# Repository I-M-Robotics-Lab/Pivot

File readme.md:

Discord: https://discord.com/invite/WJuUWsy6DJ

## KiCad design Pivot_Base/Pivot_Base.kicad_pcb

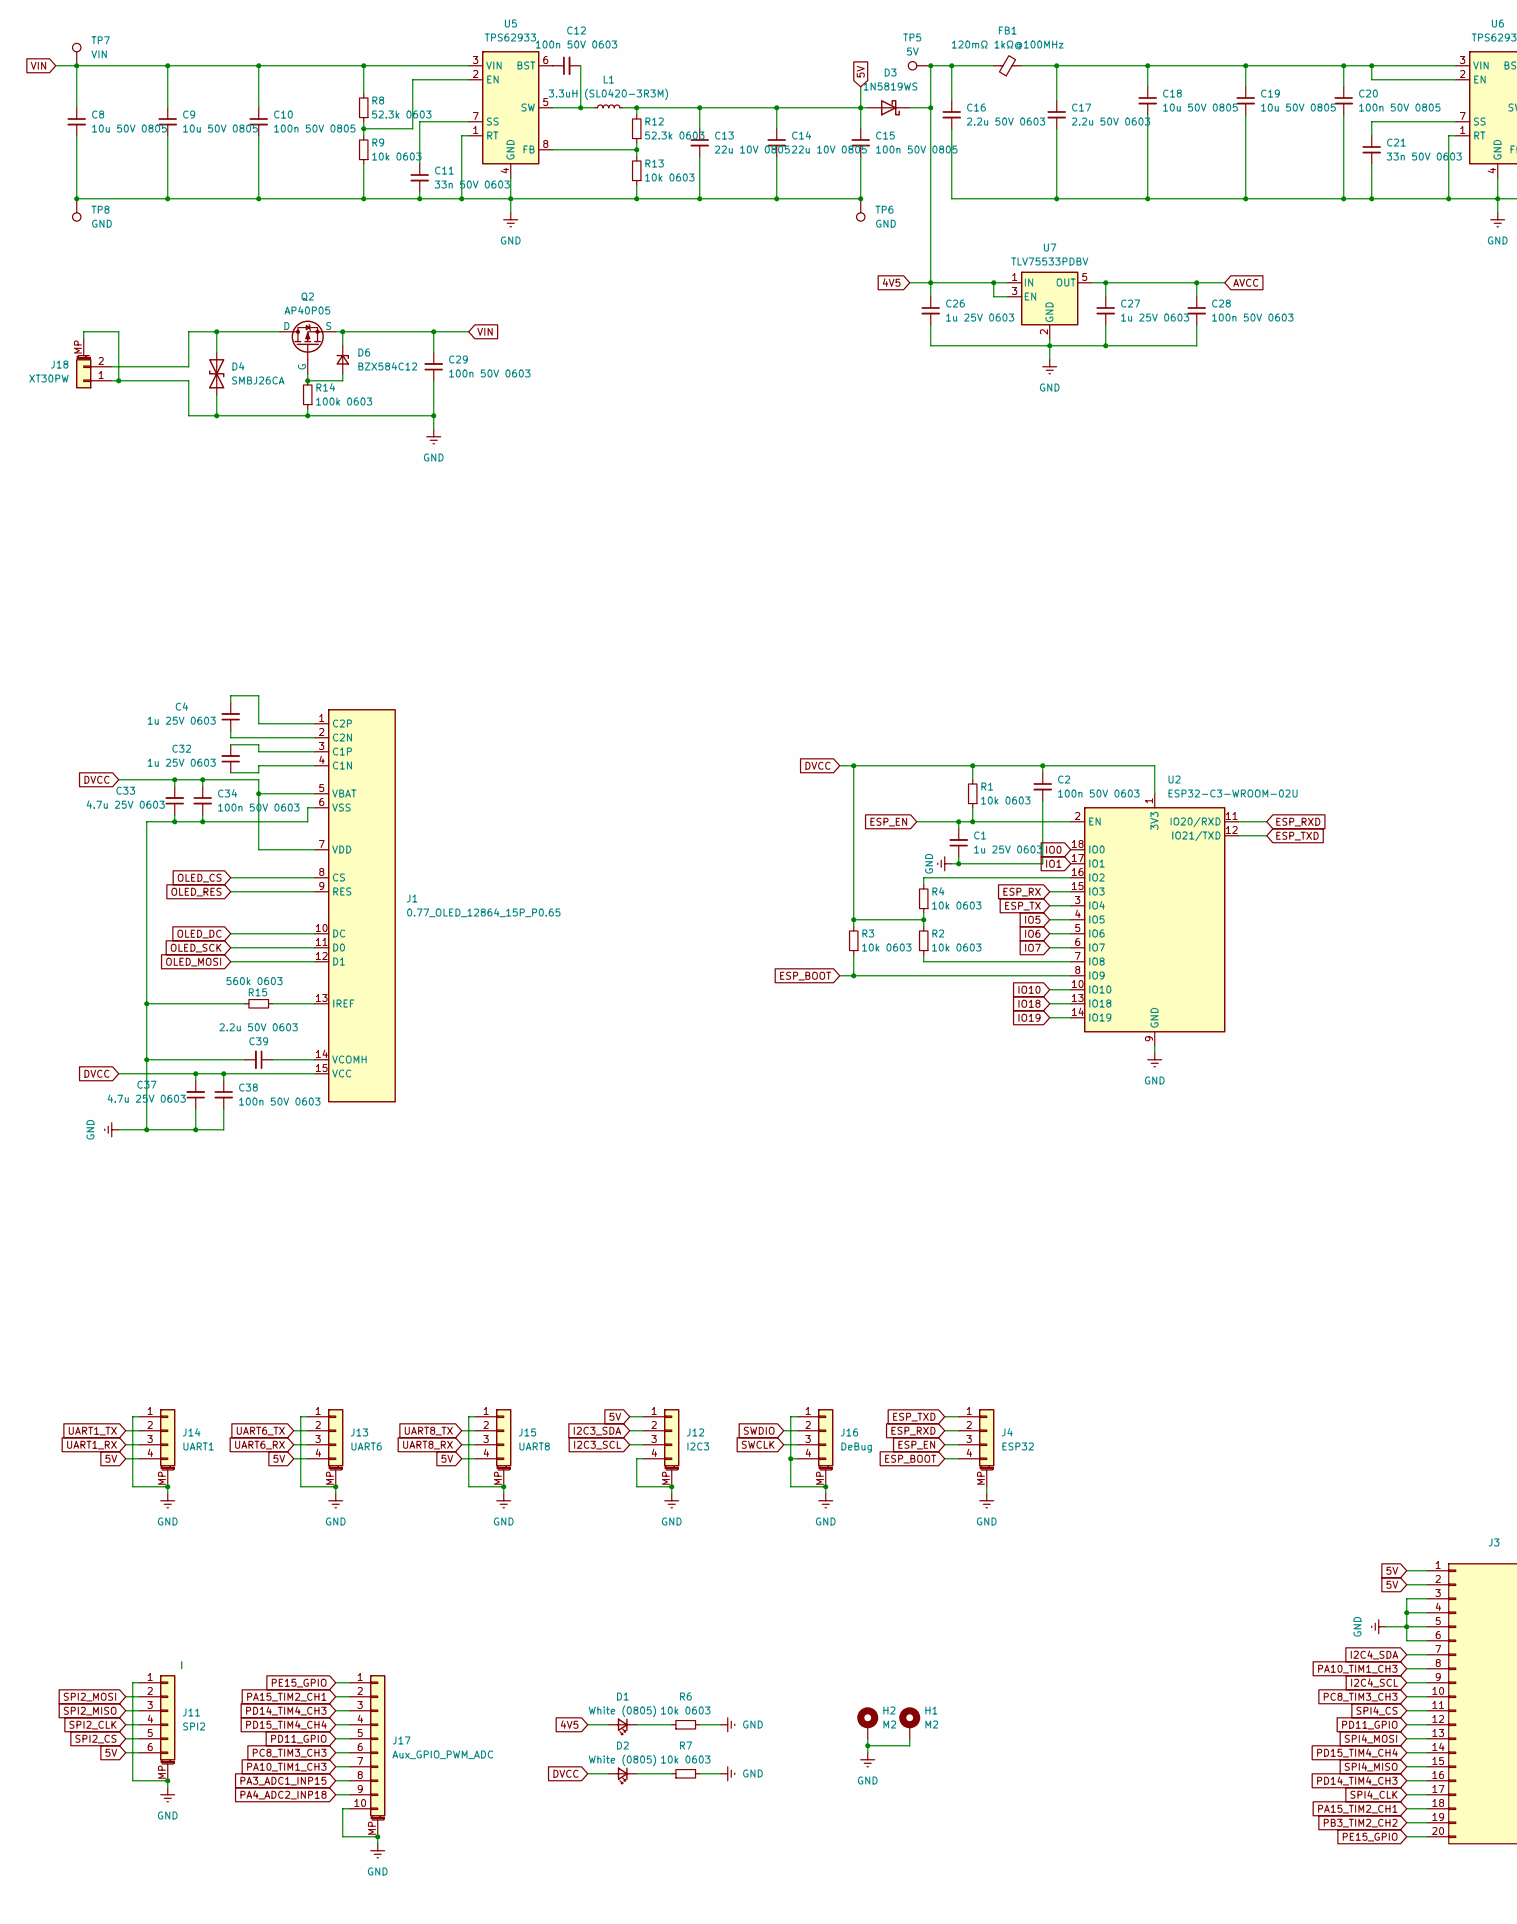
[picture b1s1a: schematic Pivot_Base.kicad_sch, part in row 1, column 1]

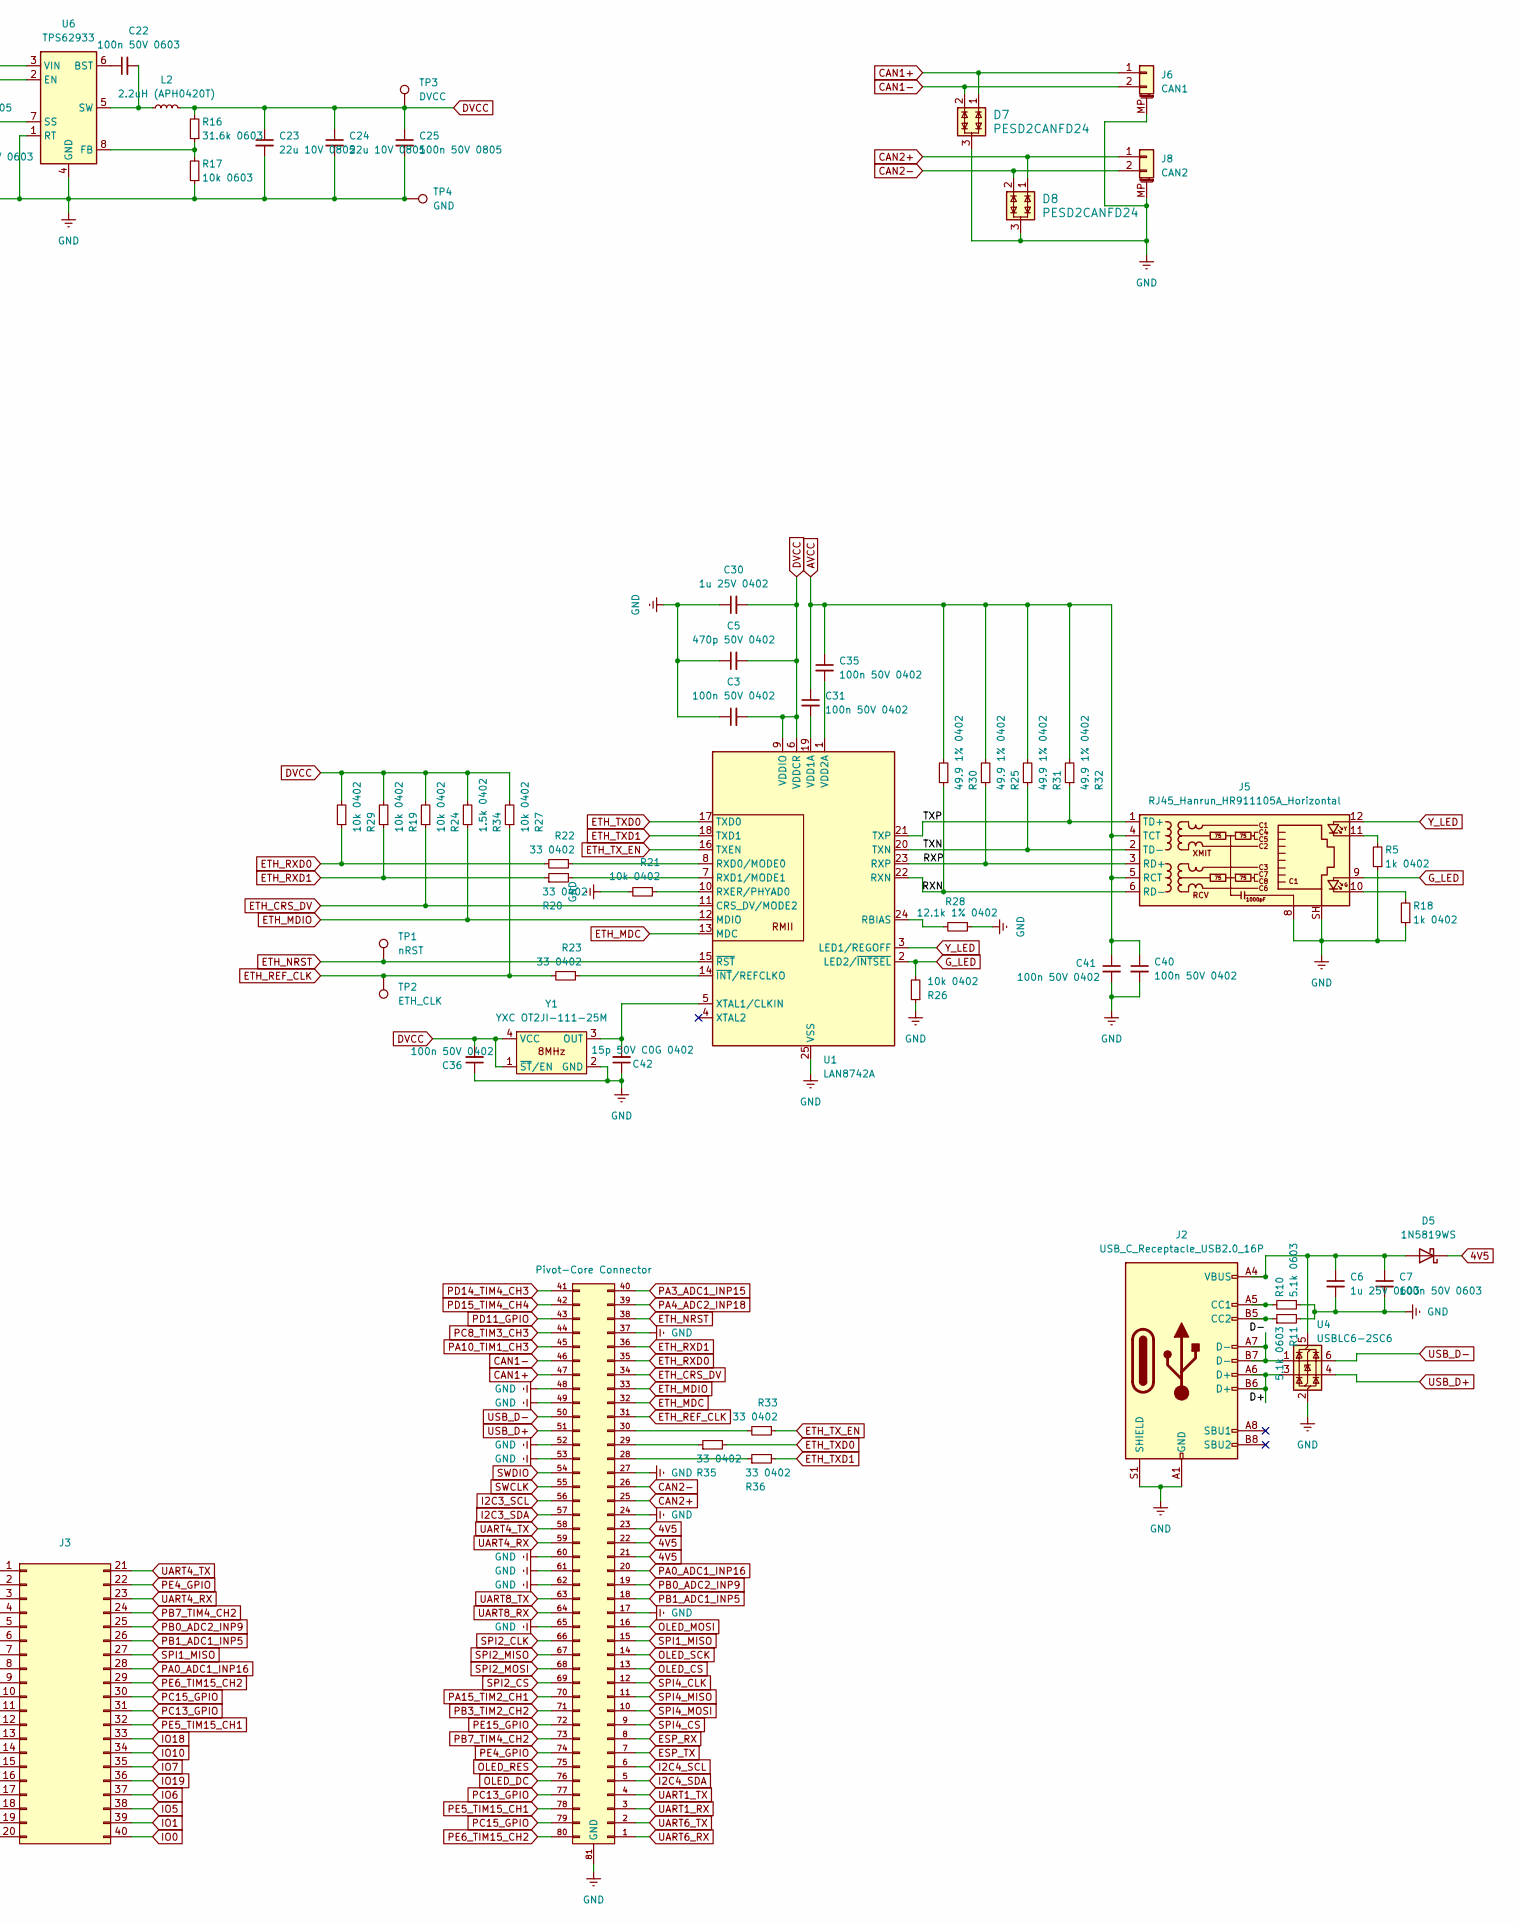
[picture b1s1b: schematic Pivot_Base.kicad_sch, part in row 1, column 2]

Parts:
C1, C4, C6, C26, C27, C32: 1u 25V 0603; C_0603_1608Metric
C2, C7, C12, C22, C28, C29, C34, C38: 100n 50V 0603; C_0603_1608Metric
C3, C31, C35, C36, C40, C41: 100n 50V 0402; C_0402_1005Metric
C5: 470p 50V 0402; C_0402_1005Metric
C8, C9, C18, C19: 10u 50V 0805; C_0805_2012Metric
C10, C15, C20, C25: 100n 50V 0805; C_0805_2012Metric
C11, C21: 33n 50V 0603; C_0603_1608Metric
C13, C14, C23, C24: 22u 10V 0805; C_0805_2012Metric
C16, C17, C39: 2.2u 50V 0603; C_0603_1608Metric
C30: 1u 25V 0402; C_0402_1005Metric
C33, C37: 4.7u 25V 0603; C_0603_1608Metric
C42: 15p 50V C0G 0402; C_0402_1005Metric
D1, D2: White (0805); LED_0805_2012Metric
D3, D5: 1N5819WS; D_SOD-323
D4: SMBJ26CA; D_SMB
D6: BZX584C12; D_SOD-523
D7, D8: PESD2CANFD24; SOT-23
FB1: 120mΩ 1kΩ@100MHz; R_0805_2012Metric
H1, H2: M2; MountingHole_2.2mm_M2_DIN965_Pad
J1: 0.77_OLED_12864_15P_P0.65
J2: USB_C_Receptacle_USB2.0_16P; USB_C_Receptacle_G-Switch_GT-USB-7010ASV
J3: PinHeader_2x20_P2.54mm_Vertical
J4: ESP32; JST_SH_SM04B-SRSS-TB_1x04-1MP_P1.00mm_Horizontal
J5: RJ45_Hanrun_HR911105A_Horizontal; HANRUN_HR911105A
J6: CAN1; JST_SH_SM02B-SRSS-TB_1x02-1MP_P1.00mm_Horizontal
J7: Pivot-Core Connector; Pivot-Core
J8: CAN2; JST_SH_SM02B-SRSS-TB_1x02-1MP_P1.00mm_Horizontal
J11: SPI2; JST_SH_SM06B-SRSS-TB_1x06-1MP_P1.00mm_Horizontal
J12: I2C3; JST_SH_SM04B-SRSS-TB_1x04-1MP_P1.00mm_Horizontal
J13: UART6; JST_SH_SM04B-SRSS-TB_1x04-1MP_P1.00mm_Horizontal
J14: UART1; JST_SH_SM04B-SRSS-TB_1x04-1MP_P1.00mm_Horizontal
J15: UART8; JST_SH_SM04B-SRSS-TB_1x04-1MP_P1.00mm_Horizontal
J16: DeBug; JST_SH_SM04B-SRSS-TB_1x04-1MP_P1.00mm_Horizontal
J17: Aux_GPIO_PWM_ADC; JST_SH_SM10B-SRSS-TB_1x10-1MP_P1.00mm_Horizontal
J18: XT30PW; AMASS_XT30PW-M_1x02_P2.50mm_Horizontal
L1: 3.3uH (SL0420-3R3M); L_Chilisin_BMRA00040420
L2: 2.2uH (APH0420T); L_APV_APH0420
Q2: AP40P05; SOT-23
R1, R2, R3, R4, R6, R7, R9, R13, R17: 10k 0603; R_0603_1608Metric
R5, R18: 1k 0402; R_0402_1005Metric
R8, R12: 52.3k 0603; R_0603_1608Metric
R10, R11: 5.1k 0603; R_0603_1608Metric
R14: 100k 0603; R_0603_1608Metric
R15: 560k 0603; R_0603_1608Metric
R16: 31.6k 0603; R_0603_1608Metric
R19, R21, R24, R26, R27, R29: 10k 0402; R_0402_1005Metric
R20, R22, R23, R33, R35, R36: 33 0402; R_0402_1005Metric
R25, R30, R31, R32: 49.9 1% 0402; R_0402_1005Metric
R28: 12.1k 1% 0402; R_0402_1005Metric
R34: 1.5k 0402; R_0402_1005Metric
TP1: nRST; TestPoint_Pad_D0.4mm
TP2: ETH_CLK; TestPoint_Pad_D0.4mm
TP3: DVCC; TestPoint_Pad_D0.4mm
TP4, TP6, TP8: GND; TestPoint_Pad_D0.4mm
TP5: 5V; TestPoint_Pad_D0.4mm
TP7: VIN; TestPoint_Pad_D0.4mm
U1: LAN8742A; VQFN-24-1EP_4x4mm_P0.5mm_EP2.5x2.5mm_ThermalVias
U2: ESP32-C3-WROOM-02U
U4: USBLC6-2SC6; SOT-23-6
U5, U6: TPS62933; SOT-583-8
U7: TLV75533PDBV; SOT-23-5
Y1: YXC OT2JI-111-25M; Crystal_SMD_3225-4Pin_3.2x2.5mm

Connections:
4V5: C16.1, C26.1, D1.2 (A), D3.1 (K), D5.1 (K), FB1.1, J7.21, J7.22, J7.23, TP5.1, U7.1 (IN), U7.3 (EN)
5V: C13.1, C14.1, C15.1, D3.2 (A), J3.1, J3.2, J11.6, J12.1, J13.4, J14.4, J15.4, L1.2, R12.2
/D+: J2.A6 (D+), J2.B6 (D+), U4.3 (I/O2)
/D-: J2.A7 (D-), J2.B7 (D-), U4.1 (I/O1)
/RXN: J5.6 (RD-), R30.1, U1.22 (RXN)
/RXP: J5.3 (RD+), R25.1, U1.23 (RXP)
/TXN: J5.2 (TD-), R31.1, U1.20 (TXN)
/TXP: J5.1 (TD+), R32.1, U1.21 (TXP)
AVCC: C27.1, C28.1, C31.1, C35.1, C40.1, C41.1, J5.4 (TCT), J5.5 (RCT), R25.2, R30.2, R31.2, R32.2, U7.5 (OUT)
CAN1+: D7.1, J6.1, J7.47
CAN1-: D7.2 (1), J6.2, J7.46
CAN2+: D8.1, J7.25, J8.1
CAN2-: D8.2 (1), J7.26, J8.2
DVCC: C2.1, C3.2, C5.2, C23.1, C24.1, C25.1, C30.2, C33.2, C34.1, C36.2, C37.2, C38.1, D2.2 (A), J1.5 (VBAT), J1.7 (VDD), J1.15 (VCC), L2.2, R1.2, R2.2, R3.2, R4.1, R16.2, R19.2, R24.2, R27.2, R29.2, R34.2, TP3.1, U1.6 (VDDCR), U1.9 (VDDIO), U2.1 (3V3), Y1.1 (~ST/EN), Y1.4 (VCC)
ESP_BOOT: J4.4, R3.1, U2.8 (IO9)
ESP_EN: C1.2, J4.3, R1.1, U2.2 (EN)
ESP_RX: J7.8, U2.15 (IO3)
ESP_RXD: J4.2, U2.11 (IO20/RXD)
ESP_TX: J7.7, U2.3 (IO4)
ESP_TXD: J4.1, U2.12 (IO21/TXD)
ETH_CRS_DV: J7.34, R24.1, U1.11 (CRS_DV/MODE2)
ETH_MDC: J7.32, U1.13 (MDC)
ETH_MDIO: J7.33, R34.1, U1.12 (MDIO)
ETH_NRST: J7.38, TP1.1, U1.15 (~RST)
ETH_REF_CLK: J7.31, R23.2, R27.1, TP2.1
ETH_RXD0: J7.35, R22.2, R29.1
ETH_RXD1: J7.36, R19.1, R20.1
ETH_TXD0: R35.2, U1.17 (TXD0)
ETH_TXD1: R36.2, U1.18 (TXD1)
ETH_TX_EN: R33.1, U1.16 (TXEN)
GND: C1.1, C2.2, C3.1, C5.1, C6.2, C7.2, C8.2, C9.2, C10.2, C11.2, C13.2, C14.2, C15.2, C16.2, C17.2, C18.2, C19.2, C20.2, C21.2, C23.2, C24.2, C25.2, C26.2, C27.2, C28.2, C29.1, C30.1, C33.1, C34.2, C36.1, C37.1, C38.2, C39.2, C40.2, C41.2, C42.1, D4.1 (A1), D7.3 (GND), D8.3 (GND), H1.1, H2.1, J1.6 (VSS), J2.A1 (GND), J2.A12 (GND), J2.B1 (GND), J2.B12 (GND), J2.S1 (SHIELD), J3.3, J3.4, J3.5, J3.6, J4.MP (MountPin), J5.8, J5.SH, J6.MP (MountPin), J7.17, J7.24, J7.27, J7.37, J7.48, J7.49, J7.52, J7.53, J7.60, J7.61, J7.62, J7.65, J7.81 (GND), J8.MP (MountPin), J11.1, J11.MP (MountPin), J12.4, J12.MP (MountPin), J13.1, J13.MP (MountPin), J14.1, J14.MP (MountPin), J15.1, J15.MP (MountPin), J16.1, J16.4, J16.MP (MountPin), J17.10, J17.MP (MountPin), J18.1, J18.MP (MountPin), R5.1, R6.2, R7.2, R9.1, R10.1, R11.2, R13.1, R14.1, R15.2, R17.1, R18.1, R21.2, R26.1, R28.1, TP4.1, TP6.1, TP8.1, U1.25 (VSS), U2.9 (GND), U2.19 (GND), U4.2 (GND), U5.1 (RT), U5.4 (GND), U6.1 (RT), U6.4 (GND), U7.2 (GND), Y1.2 (GND)
G_LED: J5.9, R26.2, U1.2 (LED2/~INTSEL)
I2C3_SCL: J7.56, J12.3
I2C3_SDA: J7.57, J12.2
I2C4_SCL: J3.9, J7.6
I2C4_SDA: J3.7, J7.5
IO0: J3.40, U2.18 (IO0)
IO1: J3.39, U2.17 (IO1)
IO5: J3.38, U2.4 (IO5)
IO6: J3.37, U2.5 (IO6)
IO7: J3.35, U2.6 (IO7)
IO10: J3.34, U2.10 (IO10)
IO18: J3.33, U2.13 (IO18)
IO19: J3.36, U2.14 (IO19)
unnamed: D1.1 (K), R6.1
unnamed: D2.1 (K), R7.1
unnamed: D4.2 (A2), J18.2, Q2.1 (D)
unnamed: C6.1, C7.1, D5.2 (A), J2.A4 (VBUS), J2.A9 (VBUS), J2.B4 (VBUS), J2.B9 (VBUS), U4.5 (VBUS)
unnamed: D6.2 (A), Q2.2 (G), R14.2
unnamed: C32.1, J1.4 (C1N)
unnamed: C32.2, J1.3 (C1P)
unnamed: C4.1, J1.2 (C2N)
unnamed: C4.2, J1.1 (C2P)
unnamed: J1.13 (IREF), R15.1
unnamed: C39.1, J1.14 (VCOMH)
unnamed: J2.A5 (CC1), R10.2
unnamed: J2.B5 (CC2), R11.1
unnamed: J5.10, R18.2
unnamed: J5.11, R5.2
unnamed: J7.28, R36.1
unnamed: J7.29, R35.1
unnamed: J7.30, R33.2
unnamed: R28.2, U1.24 (RBIAS)
unnamed: R22.1, U1.8 (RXD0/MODE0)
unnamed: R20.2, U1.7 (RXD1/MODE1)
unnamed: R21.1, U1.10 (RXER/PHYAD0)
unnamed: C31.2, U1.19 (VDD1A)
unnamed: C35.2, U1.1 (VDD2A)
unnamed: C42.2, U1.5 (XTAL1/CLKIN), Y1.3 (OUT)
unnamed: R23.1, U1.14 (~INT/REFCLKO)
unnamed: R4.2, U2.16 (IO2)
unnamed: R2.1, U2.7 (IO8)
unnamed: C12.1, U5.6 (BST)
unnamed: R8.1, R9.2, U5.2 (EN)
unnamed: R12.1, R13.2, U5.8 (FB)
unnamed: C11.1, U5.7 (SS)
unnamed: C12.2, L1.1, U5.5 (SW)
unnamed: C22.1, U6.6 (BST)
unnamed: C17.1, C18.1, C19.1, C20.1, FB1.2, U6.2 (EN), U6.3 (VIN)
unnamed: R16.1, R17.2, U6.8 (FB)
unnamed: C21.1, U6.7 (SS)
unnamed: C22.2, L2.1, U6.5 (SW)
OLED_CS: J1.8 (CS), J7.13
OLED_DC: J1.10 (DC), J7.76
OLED_MOSI: J1.12 (D1), J7.16
OLED_RES: J1.9 (RES), J7.75
OLED_SCK: J1.11 (D0), J7.14
PA0_ADC1_INP16: J3.28, J7.20
PA3_ADC1_INP15: J7.40, J17.8
PA4_ADC2_INP18: J7.39, J17.9
PA10_TIM1_CH3: J3.8, J7.45, J17.7
PA15_TIM2_CH1: J3.18, J7.70, J17.2
PB0_ADC2_INP9: J3.25, J7.19
PB1_ADC1_INP5: J3.26, J7.18
PB3_TIM2_CH2: J3.19, J7.71
PB7_TIM4_CH2: J3.24, J7.73
PC8_TIM3_CH3: J3.10, J7.44, J17.6
PC13_GPIO: J3.31, J7.77
PC15_GPIO: J3.30, J7.79
PD11_GPIO: J3.12, J7.43, J17.5
PD14_TIM4_CH3: J3.16, J7.41, J17.3
PD15_TIM4_CH4: J3.14, J7.42, J17.4
PE4_GPIO: J3.22, J7.74
PE5_TIM15_CH1: J3.32, J7.78
PE6_TIM15_CH2: J3.29, J7.80
PE15_GPIO: J3.20, J7.72, J17.1
SPI1_MISO: J3.27, J7.15
SPI2_CLK: J7.66, J11.4
SPI2_CS: J7.69, J11.5
SPI2_MISO: J7.67, J11.3
SPI2_MOSI: J7.68, J11.2
SPI4_CLK: J3.17, J7.12
SPI4_CS: J3.11, J7.9
SPI4_MISO: J3.15, J7.11
SPI4_MOSI: J3.13, J7.10
SWCLK: J7.55, J16.3
SWDIO: J7.54, J16.2
UART1_RX: J7.3, J14.3
UART1_TX: J7.4, J14.2
UART4_RX: J3.23, J7.59
UART4_TX: J3.21, J7.58
UART6_RX: J7.1, J13.3
UART6_TX: J7.2, J13.2
UART8_RX: J7.64, J15.3
UART8_TX: J7.63, J15.2
USB_D+: J7.51, U4.4 (I/O2)
USB_D-: J7.50, U4.6 (I/O1)
VIN: C8.1, C9.1, C10.1, C29.2, D6.1 (K), Q2.3 (S), R8.2, TP7.1, U5.3 (VIN)
Y_LED: J5.12, U1.3 (LED1/REGOFF)

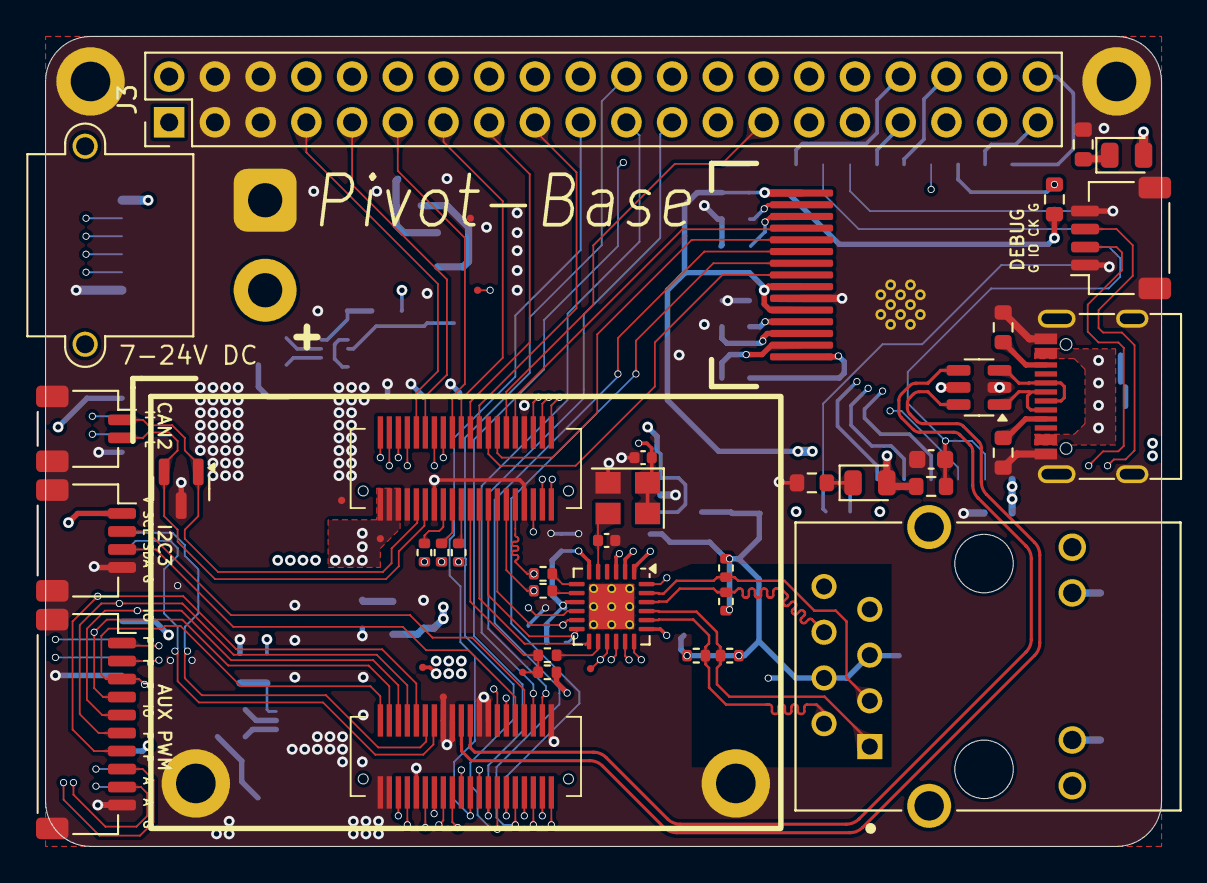
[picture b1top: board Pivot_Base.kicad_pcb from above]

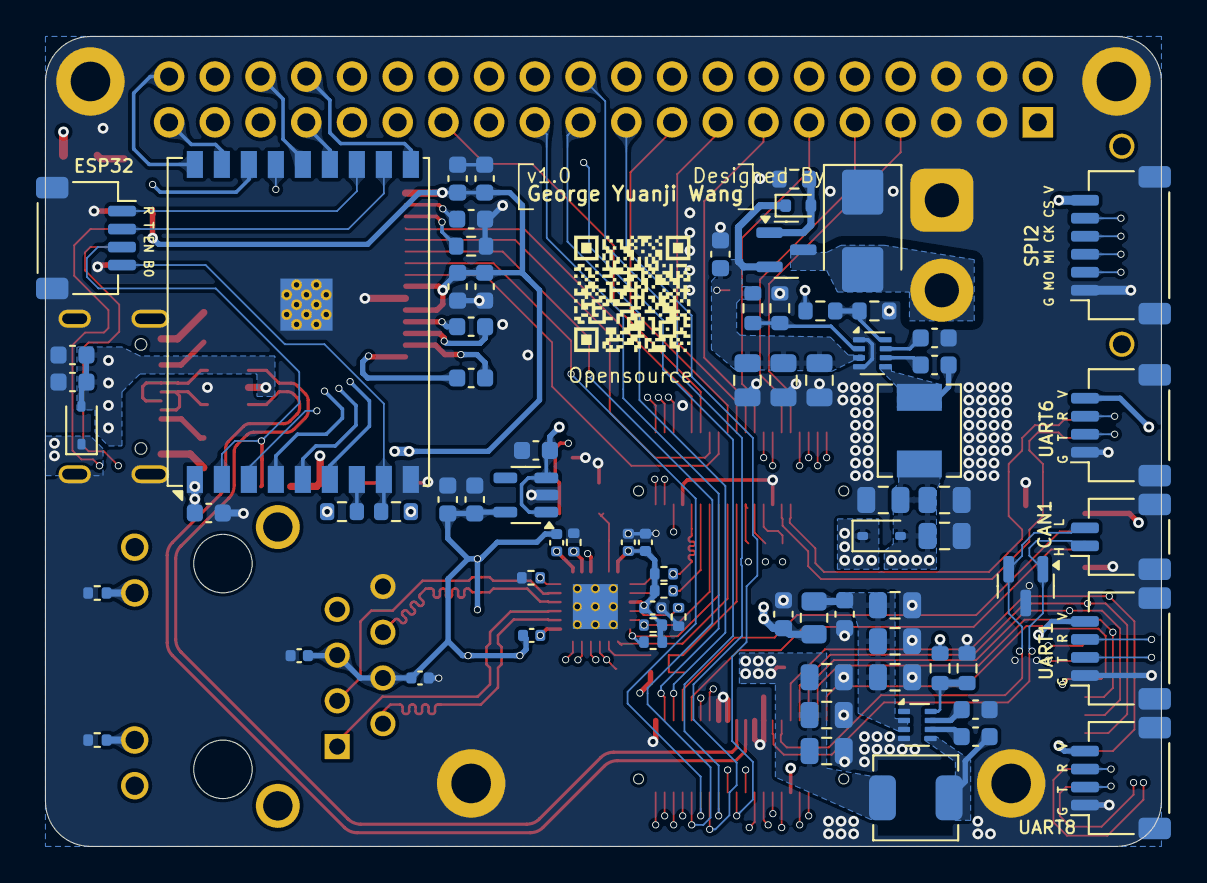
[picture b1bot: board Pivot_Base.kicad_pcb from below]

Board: 6 copper layers, 62.0 x 45.0 mm, 123 parts (77 on the bottom side), 129 nets.

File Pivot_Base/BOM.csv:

"Reference","Value","Datasheet","Footprint","Qty","DNP"
"C1,C4,C6,C26,C27,C32","1u 25V 0603","~","Capacitor_SMD:C_0603_1608Metric","6",""
"C2,C7,C12,C22,C28,C29,C34,C38","100n 50V 0603","~","Capacitor_SMD:C_0603_1608Metric","8",""
"C3,C31,C35,C36,C40,C41","100n 50V 0402","~","Capacitor_SMD:C_0402_1005Metric","6",""
"C5","470p 50V 0402","~","Capacitor_SMD:C_0402_1005Metric","1",""
"C8,C9,C18,C19","10u 35V 0805","~","Capacitor_SMD:C_0805_2012Metric","4",""
"C10,C15,C20,C25","100n 50V 0805","~","Capacitor_SMD:C_0805_2012Metric","4",""
"C11,C21","33n 50V 0603","~","Capacitor_SMD:C_0603_1608Metric","2",""
"C13,C14","22u 16V 0805","~","Capacitor_SMD:C_0805_2012Metric","2",""
"C16,C17,C39","2.2u 50V 0603","~","Capacitor_SMD:C_0603_1608Metric","3",""
"C23,C24","22u 25V 0805","~","Capacitor_SMD:C_0805_2012Metric","2",""
"C30","1u 25V 0402","~","Capacitor_SMD:C_0402_1005Metric","1",""
"C33,C37","4.7u 25V 0603","~","Capacitor_SMD:C_0603_1608Metric","2",""
"C42","15p 50V C0G 0402","~","Capacitor_SMD:C_0402_1005Metric","1",""
"D1,D2","White (0805)","~","LED_SMD:LED_0805_2012Metric","2",""
"D3,D5","1N5819WS","https://datasheet.lcsc.com/lcsc/2204281430_Guangdong-Hottech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","Diode_SMD:D_SOD-323","2",""
"D4","SMBJ26CA","~","Diode_SMD:D_SMB","1",""
"D6","BZX584C12","~","Diode_SMD:D_SOD-523","1",""
"D7,D8","PESD2CANFD24","https://www.lcsc.com/datasheet/C5278878.pdf","Package_TO_SOT_SMD:SOT-23","2",""
"FB1","120mΩ 1kΩ@100MHz","~","Resistor_SMD:R_0805_2012Metric","1",""
"J1","0.77_OLED_12864_15P_P0.65","https://www.lcsc.com/datasheet/C5123562.pdf","Pivot_Base:0.77_OLED_12864_15P_P0.65","1",""
"J2","USB_C_Receptacle_USB2.0_16P","https://www.usb.org/sites/default/files/documents/usb_type-c.zip","Connector_USB:USB_C_Receptacle_G-Switch_GT-USB-7010ASV","1",""
"J3","~","","Connector_PinHeader_2.54mm:PinHeader_2x20_P2.54mm_Vertical","1",""
"J4","ESP32","~","Connector_JST:JST_SH_SM04B-SRSS-TB_1x04-1MP_P1.00mm_Horizontal","1",""
"J5","RJ45_Hanrun_HR911105A_Horizontal","https://datasheet.lcsc.com/lcsc/1811141815_HANRUN-Zhongshan-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","Pivot_Base:HANRUN_HR911105A","1",""
"J6","CAN1","~","Connector_JST:JST_SH_SM02B-SRSS-TB_1x02-1MP_P1.00mm_Horizontal","1",""
"J7","Pivot-Core Connector","","Pivot_Base:Pivot-Core","1",""
"J8","CAN2","~","Connector_JST:JST_SH_SM02B-SRSS-TB_1x02-1MP_P1.00mm_Horizontal","1",""
"J11","SPI2","~","Connector_JST:JST_SH_SM06B-SRSS-TB_1x06-1MP_P1.00mm_Horizontal","1",""
"J12","I2C3","~","Connector_JST:JST_SH_SM04B-SRSS-TB_1x04-1MP_P1.00mm_Horizontal","1",""
"J13","UART6","~","Connector_JST:JST_SH_SM04B-SRSS-TB_1x04-1MP_P1.00mm_Horizontal","1",""
"J14","UART1","~","Connector_JST:JST_SH_SM04B-SRSS-TB_1x04-1MP_P1.00mm_Horizontal","1",""
"J15","UART8","~","Connector_JST:JST_SH_SM04B-SRSS-TB_1x04-1MP_P1.00mm_Horizontal","1",""
"J16","DeBug","~","Connector_JST:JST_SH_SM04B-SRSS-TB_1x04-1MP_P1.00mm_Horizontal","1",""
"J17","Aux_GPIO_PWM_ADC","~","Connector_JST:JST_SH_SM10B-SRSS-TB_1x10-1MP_P1.00mm_Horizontal","1",""
"J18","XT30PW","~","Connector_AMASS:AMASS_XT30PW-M_1x02_P2.50mm_Horizontal","1",""
"L1","3.3uH (SL0420-3R3M)","https://www.lcsc.com/datasheet/C22463807.pdf","Inductor_SMD:L_Chilisin_BMRA00040420","1",""
"L2","2.2uH (APH0420T)","https://lcsc.com/datasheet/lcsc_datasheet_2409302232_APV-APH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","Inductor_SMD:L_APV_APH0420","1",""
"Q2","AP40P05","https://www.lcsc.com/datasheet/C2886385.pdf","Package_TO_SOT_SMD:SOT-23","1",""
"R1,R2,R3,R4,R6,R7,R9,R13,R17","10k 0603","~","Resistor_SMD:R_0603_1608Metric","9",""
"R5,R18","1k 0402","~","Resistor_SMD:R_0402_1005Metric","2",""
"R8,R12","52.5k 0603","~","Resistor_SMD:R_0603_1608Metric","2",""
"R10,R11","5.1k 0603","~","Resistor_SMD:R_0603_1608Metric","2",""
"R14","100k 0603","~","Resistor_SMD:R_0603_1608Metric","1",""
"R15","560k 0603","~","Resistor_SMD:R_0603_1608Metric","1",""
"R16","31.3k 0603","~","Resistor_SMD:R_0603_1608Metric","1",""
"R19,R21,R24,R26,R27,R29","10k 0402","~","Resistor_SMD:R_0402_1005Metric","6",""
"R20,R22,R23,R33,R35,R36","33 0402","~","Resistor_SMD:R_0402_1005Metric","6",""
"R25,R30,R31,R32","49.9 1% 0402","~","Resistor_SMD:R_0402_1005Metric","4",""
"R28","12.1k 1% 0402","~","Resistor_SMD:R_0402_1005Metric","1",""
"R34","1.5k 0402","~","Resistor_SMD:R_0402_1005Metric","1",""
"TP1","nRST","~","TestPoint:TestPoint_Pad_D0.4mm","1",""
"TP2","ETH_CLK","~","TestPoint:TestPoint_Pad_D0.4mm","1",""
"TP3","DVCC","~","TestPoint:TestPoint_Pad_D0.4mm","1",""
"TP4,TP6,TP8","GND","~","TestPoint:TestPoint_Pad_D0.4mm","3",""
"TP5","5V","~","TestPoint:TestPoint_Pad_D0.4mm","1",""
"TP7","VIN","~","TestPoint:TestPoint_Pad_D0.4mm","1",""
"U1","LAN8742A","http://ww1.microchip.com/downloads/en/DeviceDoc/8742a.pdf","Package_DFN_QFN:VQFN-24-1EP_4x4mm_P0.5mm_EP2.5x2.5mm_ThermalVias","1",""
"U2","ESP32-C3-WROOM-02U","https://www.espressif.com/sites/default/files/documentation/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","RF_Module:ESP32-C3-WROOM-02U","1",""
"U4","USBLC6-2SC6","https://www.st.com/resource/en/datasheet/usblc6-2.pdf","Package_TO_SOT_SMD:SOT-23-6","1",""
"U5,U6","TPS62933","https://www.ti.com/lit/ds/symlink/tps62933.pdf","Package_TO_SOT_SMD:SOT-583-8","2",""
"U7","TLV75533PDBV","http://www.ti.com/lit/ds/symlink/tlv755p.pdf","Package_TO_SOT_SMD:SOT-23-5","1",""
"Y1","YXC OT2JI-111-25M","https://www.lcsc.com/datasheet/C20617587.pdf","Crystal:Crystal_SMD_3225-4Pin_3.2x2.5mm","1",""

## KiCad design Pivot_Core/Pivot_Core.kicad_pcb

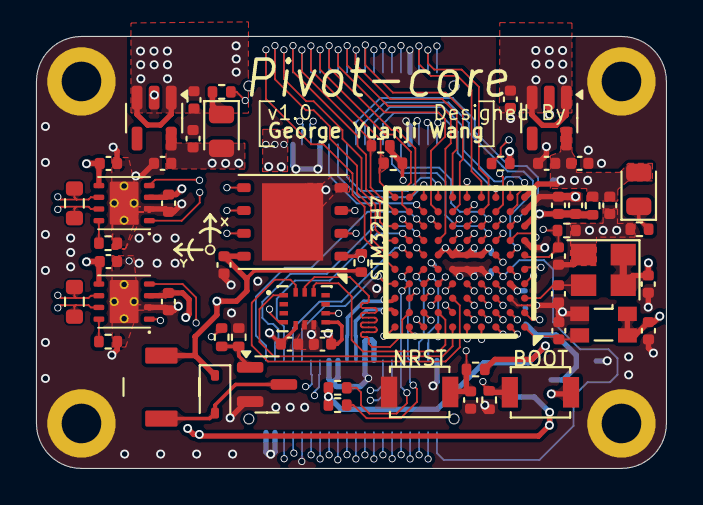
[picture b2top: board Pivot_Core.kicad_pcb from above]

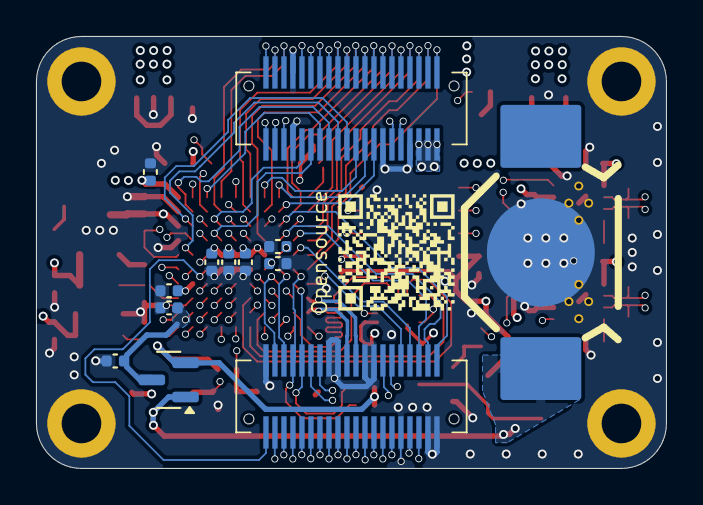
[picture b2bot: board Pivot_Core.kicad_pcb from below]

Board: 6 copper layers, 35.0 x 24.0 mm, 73 parts (13 on the bottom side), 103 nets.

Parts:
BT1: Battery_Cell; BatteryClip-MY-927-02
BZ1: FUET-4020
C1, C2, C3, C4, C5, C9, C10, C11, C12, C14, C16, C19, C20, C24, C25, C26, C27, C28, C32: 100n; C_0402_1005Metric
C6, C7, C8, C17, C18, C33, C34: 1u; C_0402_1005Metric
C13, C15: 15p; C_0402_1005Metric
C21: 4.7u; C_0402_1005Metric
C22, C23: 2.2u; C_0402_1005Metric
D1: Blue (0805); LED_0805_2012Metric
D2: Green (0805); LED_0805_2012Metric
D3: 1N5819WS; D_SOD-323
D4: BAT54C; SOT-23
FB1: 100mΩ 600Ω @100MHz; R_0402_1005Metric
H1, H2, H3, H4: M2; MountingHole_2.2mm_M2_DIN965_Pad
J1, J2: B2B-40P-P0.5 Connector; B2B-40P-P0.5
Q1: AO3400A; SOT-23
R1, R2: 1k; R_0402_1005Metric
R3: 100; R_0402_1005Metric
R4: 100k; R_0402_1005Metric
R5: 3.3k; R_0402_1005Metric
R6, R8, R9, R10, R12: 10k; R_0402_1005Metric
R7, R11: 120; R_0603_1608Metric
R13, R14, R15, R16: 4.7k; R_0402_1005Metric
SW1(B3U-1000)1, SW2(B3U-1000)1: SW_Push; SW_SPST_B3U-1000P
TH1: 10k; R_0402_1005Metric
U1: STM32H743VIHx; TFBGA-100_8x8mm_Layout10x10_P0.8mm
U2: W25Q128JVP; WSON-8-1EP_6x5mm_P1.27mm_EP3.4x4.3mm
U3: BMI270; XDCR_BMI270
U5, U7: TCAN1051HVDRB; TCAN1051VDRB
U8, U9: TLV75533PDBV; SOT-23-5
Y1: YXC_OT2EL4C4JI-111OLP-8M; Crystal_SMD_3225-4Pin_3.2x2.5mm
Y2: SG-3030CM/X1B0002110001; Oscillator_SMD_SeikoEpson_SG3030CM

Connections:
5V_VIN: C4.1, C6.1, C9.1, C17.1, J1.1, J1.2, J1.3, U5.3 (VCC), U7.3 (VCC), U8.1 (IN), U8.3 (EN), U9.1 (IN), U9.3 (EN)
AVCC: C32.2, C33.2, FB1.2, TH1.1, U1.H1 (VDDA)
BOOT0: R10.2, SW2(B3U-1000)1.1, U1.D5 (BOOT0)
Buzzer_PWM: R3.2, U1.C9 (PA9)
CAN1+: J2.14, R11.1, U7.7 (CANH)
CAN1-: J2.15, R11.2, U7.6 (CANL)
CAN2+: J1.5, R7.1, U5.7 (CANH)
CAN2-: J1.6, R7.2, U5.6 (CANL)
DVCC_Core: C7.1, C12.2, C14.2, C16.1, C24.2, C25.2, C26.2, C27.2, C28.2, C34.2, D1.2 (A), D4.2, FB1.1, R9.2, R13.1, R14.2, R15.2, R16.1, SW2(B3U-1000)1.2, U1.D2 (VDD), U1.F4 (VDDLDO), U1.F5 (VDD), U1.F6 (VDD33_USB), U1.F7 (PDR_ON), U1.K1 (VDD), U8.5 (OUT), Y1.1 (~ST/EN), Y1.4 (VCC), Y2.1 (~ST/EN), Y2.4 (VCC)
DVCC_Periph: BZ1.1 (+), C1.1, C2.1, C3.1, C5.1, C10.1, C18.1, C19.1, D2.2 (A), D3.1 (K), R12.2, U2.8 (VCC), U3.5 (VDDIO), U3.8 (VDD), U5.5 (VIO), U7.5 (VIO), U9.5 (OUT)
ETH_CRS_DV: J1.14, U1.K3 (PA7)
ETH_MDC: J1.12, U1.F2 (PC1)
ETH_MDIO: J1.13, U1.J2 (PA2)
ETH_REF_CLK: J1.11, U1.H2 (PA1)
ETH_RXD0: J1.15, U1.G4 (PC4)
ETH_RXD1: J1.16, U1.H4 (PC5)
ETH_TXD0: J1.9, U1.K8 (PB12)
ETH_TXD1: J1.8, U1.J8 (PB13)
ETH_TX_EN: J1.10, U1.K7 (PB11)
FDCAN1_RX: U1.B4 (PB8), U7.4 (RXD)
FDCAN1_TX: U1.A4 (PB9), U7.1 (TXD)
FDCAN2_RX: U1.C5 (PB5), U5.4 (RXD)
FDCAN2_TX: U1.B5 (PB6), U5.1 (TXD)
GND: BT1.2 (-), C1.2, C2.2, C3.2, C4.2, C5.2, C6.2, C7.2, C8.2, C9.2, C10.2, C11.1, C12.1, C13.1, C14.1, C15.1, C16.2, C17.2, C18.2, C19.2, C20.1, C21.1, C22.1, C23.1, C24.1, C25.1, C26.1, C27.1, C28.1, C32.1, C33.1, C34.1, H1.1, H2.1, H3.1, H4.1, J1.4, J1.7, J1.17, J1.37, J2.1, J2.8, J2.9, J2.12, J2.13, J2.36, J2.39, J2.40, Q1.2 (S), R1.2, R4.2, R5.1, R6.2, R8.2, R10.1, SW1(B3U-1000)1.2, U1.C2 (VSS), U1.E4 (VSS), U1.E5 (VSS), U1.E6 (VSS), U1.G1 (VSSA), U1.J1 (VSS), U2.4 (GND), U3.6 (GNDIO), U3.7 (GND), U5.2 (GND), U7.2 (GND), U8.2 (GND), U9.2 (GND), Y1.2 (GND), Y2.2 (GND)
I2C3_SCL: J2.5, R14.1, U1.D9 (PA8)
I2C3_SDA: J2.4, R16.2, U1.E9 (PC9)
I2C4_SCL: J1.26, R15.1, U1.K10 (PD12)
I2C4_SDA: J1.25, R13.2, U1.J10 (PD13)
IMU_INT1: U1.H9 (PD10), U3.4 (INT1)
IMU_INT2: U1.C8 (PC12), U3.9 (INT2)
IMU_SPI3_CLK: U1.B9 (PC10), U3.13 (SCX)
IMU_SPI3_CS: U1.B7 (PD2), U3.12 (CSB)
IMU_SPI3_MISO: U1.A6 (PB4), U3.1 (SDO)
IMU_SPI3_MOSI: U1.C6 (PD6), U3.14 (SDX)
LED_GREEN: R2.2, U1.B6 (PD5)
NRST: C11.2, R9.1, SW1(B3U-1000)1.1, U1.E1 (NRST)
unnamed: BT1.1 (+), D4.1
unnamed: BZ1.2 (-), D3.2 (A), Q1.3 (D)
unnamed: C22.2, U1.F8 (VCAP)
unnamed: C23.2, U1.E7 (VCAP)
unnamed: D1.1 (K), R1.1
unnamed: D2.1 (K), R2.1
unnamed: Q1.1 (G), R3.1, R4.1
unnamed: C15.2, U1.A1 (PC14), Y2.3 (OUT)
unnamed: C13.2, U1.C1 (PH0), Y1.3 (OUT)
unnamed: C20.2, C21.2, D4.3, U1.B2 (VBAT)
unnamed: R6.1, U5.8 (S)
unnamed: R8.1, U7.8 (S)
PA0_ADC1_INP16: J1.40, U1.G2 (PA0)
PA3_ADC1_INP15: J1.20, U1.K2 (PA3)
PA4_ADC2_INP18: J1.19, U1.G3 (PA4)
PA10_TIM1_CH3: J2.16, U1.D10 (PA10)
PA15_TIM2_CH1: J2.31, U1.A8 (PA15)
PB0_ADC2_INP9: J1.39, U1.J4 (PB0)
PB1_ADC1_INP5: J1.38, U1.K4 (PB1)
PB3_TIM2_CH2: J2.30, U1.A7 (PB3)
PB7_TIM4_CH2: J2.28, U1.A5 (PB7)
PC8_TIM3_CH3: J2.17, U1.F9 (PC8)
PC13_GPIO: J2.24, U1.A2 (PC13)
PC15_GPIO: J2.22, U1.B1 (PC15)
PD11_GPIO: J2.18, U1.G9 (PD11)
PD14_TIM4_CH3: J2.20, U1.H8 (PD14)
PD15_TIM4_CH4: J2.19, U1.G8 (PD15)
PE2_GPIO: J2.26, U1.A3 (PE2)
PE3_GPIO: J2.25, U1.B3 (PE3)
PE4_GPIO: J2.27, U1.C3 (PE4)
PE5_TIM15_CH1: J2.23, U1.D3 (PE5)
PE6_TIM15_CH2: J2.21, U1.E3 (PE6)
PE11_GPIO: J1.18, U1.H6 (PE11)
PE15_GPIO: J2.29, U1.H7 (PE15)
QSPI_CLK: U1.G5 (PB2), U2.6 (CLK)
QSPI_CS: R12.1, U1.B8 (PC11), U2.1 (~CS)
QSPI_IO0: U1.H5 (PE7), U2.5 (DI(IO0))
QSPI_IO1: U1.J5 (PE8), U2.2 (DO(IO1))
QSPI_IO2: U1.K5 (PE9), U2.3 (IO2)
QSPI_IO3: U1.G6 (PE10), U2.7 (IO3)
SPI1_CLK: J1.34, U1.H3 (PA5)
SPI1_CS: J1.33, U1.D7 (PD4)
SPI1_MISO: J1.35, U1.J3 (PA6)
SPI1_MOSI: J1.36, U1.D6 (PD7)
SPI2_CLK: J2.35, U1.C7 (PD3)
SPI2_CS: J2.32, U1.D1 (PH1)
SPI2_MISO: J2.34, U1.E2 (PC2_C)
SPI2_MOSI: J2.33, U1.F3 (PC3_C)
SPI4_CLK: J1.32, U1.J6 (PE12)
SPI4_CS: J1.29, U1.J7 (PB10)
SPI4_MISO: J1.31, U1.K6 (PE13)
SPI4_MOSI: J1.30, U1.G7 (PE14)
SWCLK: J2.6, U1.A9 (PA14)
SWDIO: J2.7, U1.A10 (PA13)
TEMP_Sense: C8.1, R5.2, TH1.2, U1.F1 (PC0)
UART1_RX: J1.23, U1.G10 (PB15)
UART1_TX: J1.24, U1.H10 (PB14)
UART3_RX: J1.27, U1.J9 (PD9)
UART3_TX: J1.28, U1.K9 (PD8)
UART4_RX: J2.2, U1.D8 (PD0)
UART4_TX: J2.3, U1.E8 (PD1)
UART6_RX: J1.21, U1.E10 (PC7)
UART6_TX: J1.22, U1.F10 (PC6)
UART8_RX: J2.37, U1.D4 (PE0)
UART8_TX: J2.38, U1.C4 (PE1)
USB_D+: J2.10, U1.B10 (PA12)
USB_D-: J2.11, U1.C10 (PA11)

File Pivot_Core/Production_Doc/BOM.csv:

"Designator","Comment","Footprint","Qty","DNP","Part Number"
"BT1","Battery_Cell","1_my_custom:BatteryClip-MY-927-02","1","","C2902336"
"BZ1","FUET-4020","Pivot_Core:FUET-4020","1","","C391027"
"C1,C2,C3,C4,C5,C9,C10,C11,C12,C14,C16,C19,C20,C24,C25,C26,C27,C28,C32","100n, 50V, X7R","Capacitor_SMD:C_0402_1005Metric","19","","C307331"
"C6,C7,C8,C17,C18,C33,C34","1u, 25V, X7R","Capacitor_SMD:C_0402_1005Metric","7","","C52923"
"C13,C15","15p, 50V, C0G","Capacitor_SMD:C_0402_1005Metric","2","","C1548"
"C21","4.7u, 10V, X7R","Capacitor_SMD:C_0402_1005Metric","1","","C23733"
"C22,C23","2.2u, 6.3V, X7R","Capacitor_SMD:C_0402_1005Metric","2","","C12530"
"D1","Blue (0805)","LED_SMD:LED_0805_2012Metric","1","","C34499"
"D2","Green (0805)","LED_SMD:LED_0805_2012Metric","1","","C2297"
"D3","1N5819WS","Diode_SMD:D_SOD-323","1","","C191023"
"D4","BAT54C","Package_TO_SOT_SMD:SOT-23","1","","BAT54C"
"FB1","100mΩ 600Ω @100MHz","Resistor_SMD:R_0402_1005Metric","1","","C160977"
"J1,J2","B2B-40P-P0.5 Connector","Pivot_Core:B2B-40P-P0.5","2","","C41421098"
"Q1","AO3400A","Package_TO_SOT_SMD:SOT-23","1","","C20917"
"R1,R2","1k","Resistor_SMD:R_0402_1005Metric","2","","C11702"
"R3","100","Resistor_SMD:R_0402_1005Metric","1","","C25076"
"R4","100k","Resistor_SMD:R_0402_1005Metric","1","","C25741"
"R5","3.3k","Resistor_SMD:R_0402_1005Metric","1","","C25890"
"R6,R8,R9,R10,R12","10k","Resistor_SMD:R_0402_1005Metric","5","","C25744"
"TH1", "Thermistor:R_0402_1005Metric","1","","C77131"
"R7,R11","120","Resistor_SMD:R_0603_1608Metric","2","","C22787"
"R13,R14,R15,R16","4.7k","Resistor_SMD:R_0402_1005Metric","4","","C25900"
"SW1(B3U-1000)1,SW2(B3U-1000)1","SW_Push","Button_Switch_SMD:SW_SPST_B3U-1000P","2","","C231329"
"U1","STM32H743VIHx","Package_BGA:TFBGA-100_8x8mm_Layout10x10_P0.8mm","1","","C964146"
"U2","W25Q128JVP","Package_SON:WSON-8-1EP_6x5mm_P1.27mm_EP3.4x4.3mm","1","","C190862"
"U3","BMI270","Pivot_Core:XDCR_BMI270","1","","C2836813"
"U5,U7","TCAN1051HVDRB","1_my_custom:TCAN1051VDRB","2","","C2671825"
"U8,U9","TLV75533PDBV","Package_TO_SOT_SMD:SOT-23-5","2","","C404027"
"Y1","YXC_OT2EL4C4JI-111OLP-8M","Crystal:Crystal_SMD_3225-4Pin_3.2x2.5mm","1","","C5189450"
"Y2","SG-3030CM/X1B0002110001","Oscillator:Oscillator_SMD_SeikoEpson_SG3030CM","1","","C256005"

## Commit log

2026-01-07 First Commit, Hardware Files
2026-01-07 Add Discord invite link to README
